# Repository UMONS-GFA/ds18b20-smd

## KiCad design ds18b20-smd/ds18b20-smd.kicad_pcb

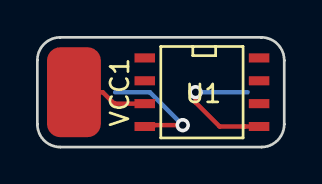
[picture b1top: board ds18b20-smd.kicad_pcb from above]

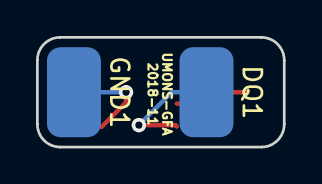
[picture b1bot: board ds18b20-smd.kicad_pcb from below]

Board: 2 copper layers, 13.7 x 6.1 mm, 4 parts (2 on the bottom side), 3 nets.

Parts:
DQ1: Pad; PAD3mmx5mm
GND1: Pad; PAD3mmx5mm
U1: DS18B20Z; SOIC-8-N
VCC1: Pad; PAD3mmx5mm

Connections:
DQ: DQ1.1, U1.4
GND: GND1.1, U1.5
VCC: U1.3, VCC1.1

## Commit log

2018-11-19 update schema
2018-11-19 add missing power flags
2018-11-19 upgrade project
2018-11-19 update project
2018-11-20 ready for release
2018-11-20 add gerber zip
2018-11-22 add filled zones
